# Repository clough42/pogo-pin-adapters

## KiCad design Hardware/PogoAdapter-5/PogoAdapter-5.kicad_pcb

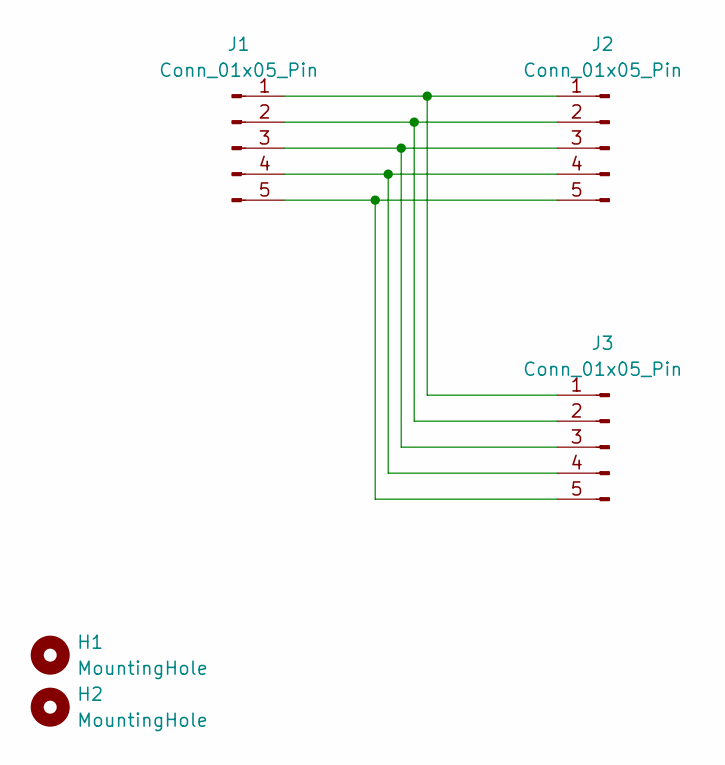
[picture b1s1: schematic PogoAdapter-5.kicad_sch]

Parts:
H1, H2: MountingHole; MountingHole_3.2mm_M3
J1, J2, J3: Conn_01x05_Pin; PinHeader_1x05_P2.54mm_Vertical

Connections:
unnamed: J1.1, J2.1, J3.1
unnamed: J1.2, J2.2, J3.2
unnamed: J1.3, J2.3, J3.3
unnamed: J1.4, J2.4, J3.4
unnamed: J1.5, J2.5, J3.5

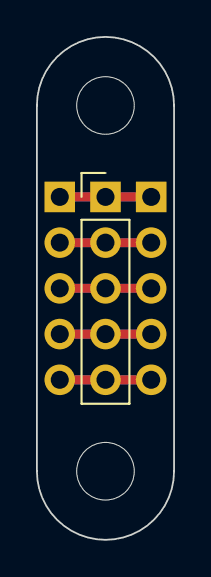
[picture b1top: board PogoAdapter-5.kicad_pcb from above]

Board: 2 copper layers, 7.6 x 27.9 mm, 5 parts (0 on the bottom side), 5 nets.

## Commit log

2023-07-18 Initial upload of 4- and 5-pin 2.54mm POGO adapter boards.
